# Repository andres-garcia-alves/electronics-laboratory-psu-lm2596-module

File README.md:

# Laboratory Power Supply Unit - LM2596 Module

Electronic adjustable laboratory power supply unit based on LM2596 DC-DC Step-Down module.  
Output 1.25-30V, max 2A, with current limitation feature.  

Based on videos (spanish):  
- [Control de Corriente para Fuente DC-DC LM2596](https://www.youtube.com/watch?v=ucfL-aOuTAA) from [KrissElectronics](https://www.youtube.com/@KrissElectronics) YouTube channel.
- [Fuente DC-DC LM2596, Control Externo Feedback](https://www.youtube.com/watch?v=mXjmIwHC1IA) from [Electgpl](https://www.youtube.com/@electgpl) YouTube channel.
- [Control de Corriente para DC-DC con LM2596, CC/CV con LM358](https://www.youtube.com/watch?v=a19zc0bWBYk) from [Electgpl](https://www.youtube.com/@electgpl) YouTube channel.

&nbsp;

This project use the following electronic components:
- 1 x LM2596 DC-DC Step-Down module (with current limitation).
- 1 x Voltimeter+Amperimeter DSN-VC288.
- 2 x Potenciometers B10K (lineal)
- 1 x Resistor 2.2ohm 15w.
- 2 x Borniers.
- 2 x 3 pins connectors.
- 1 x DC Jack female connector.

&nbsp;

### Screenshots

| Diagram - Schematics                                | Diagram - PCB                                       |
|-----------------------------------------------------|-----------------------------------------------------|
|              |                    |

| Diagram - PCB Render                                | Diagram - PCB Render                                |
|-----------------------------------------------------|-----------------------------------------------------|
|          |           |

| Diagram - Voltimeter/Amperimeter wiring             | Diagram - Current control wiring                    |
|-----------------------------------------------------|-----------------------------------------------------|
|  |         |

| Case - 3D Model                                     | Prototype                                           |
|-----------------------------------------------------|-----------------------------------------------------|
|               |                   |

| Project Assembly                                    | Project Assembly                                    |
|-----------------------------------------------------|-----------------------------------------------------|
|            |            |

| Project Final                                       | Project Final                                       |
|-----------------------------------------------------|-----------------------------------------------------|
|               |               |

| Project Final                                       | Project Final (YouTube video)                       |
|-----------------------------------------------------|-----------------------------------------------------|
|               |  |

See 'Rescources' sub-folder for more pictures & videos of the project.

&nbsp;

### Version History

v1.0 (2023.06.07) - Initial release.  
v1.1 (2023.06.28) - Update electronic diagrams, adding case 3D model.  
v1.2 (2023.07.08) - Adding 'Resources' folder.  
v1.3 (2025.12.26) - Adding 'Stickers' folder.  

&nbsp;

This source code is licensed under GPL v3.0  
Please send me your feedback about this project: andres.garcia.alves@gmail.com

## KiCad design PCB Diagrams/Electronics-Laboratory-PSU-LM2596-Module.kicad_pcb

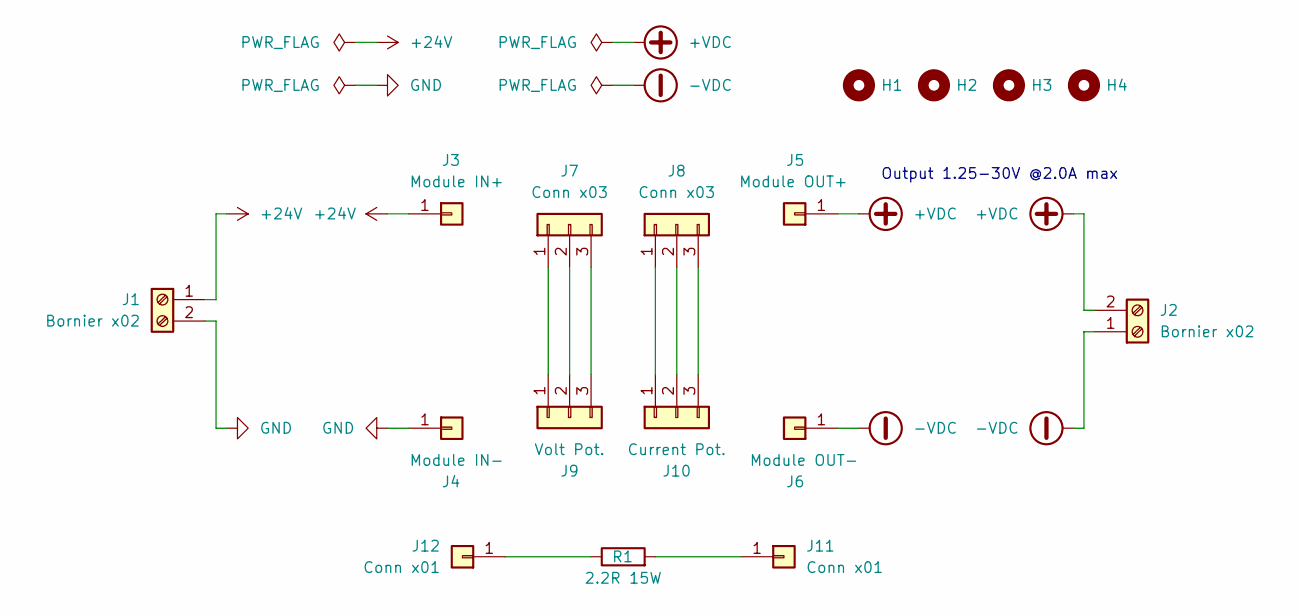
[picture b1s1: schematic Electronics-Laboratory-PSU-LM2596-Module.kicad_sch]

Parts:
H1, H2, H3, H4: MountingHole; MountingHole_2.1mm
J1, J2: Bornier x02; TerminalBlock_bornier-2_P5.08mm
J3: Module IN+; PinHeader_1x01_P2.54mm_Vertical
J4: Module IN-; PinHeader_1x01_P2.54mm_Vertical
J5: Module OUT+; PinHeader_1x01_P2.54mm_Vertical
J6: Module OUT-; PinHeader_1x01_P2.54mm_Vertical
J7, J8: Conn x03; PinHeader_1x03_P2.54mm_Vertical
J9: Volt Pot.; Molex_KK-254_AE-6410-03A_1x03_P2.54mm_Vertical
J10: Current Pot.; Molex_KK-254_AE-6410-03A_1x03_P2.54mm_Vertical
J11, J12: Conn x01; PinHeader_1x01_P2.54mm_Vertical
R1: 2.2R 15W; R_Axial_Power_L48.0mm_W12.5mm_P55.88mm

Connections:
+24V: J1.1, J3.1
+VDC: J2.2, J5.1
-VDC: J2.1, J6.1
GND: J1.2, J4.1
unnamed: J7.1, J9.1
unnamed: J7.2, J9.2
unnamed: J7.3, J9.3
unnamed: J8.1, J10.1
unnamed: J8.2, J10.2
unnamed: J8.3, J10.3
unnamed: J11.1, R1.2
unnamed: J12.1, R1.1

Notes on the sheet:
Output 1.25-30V @2.0A max

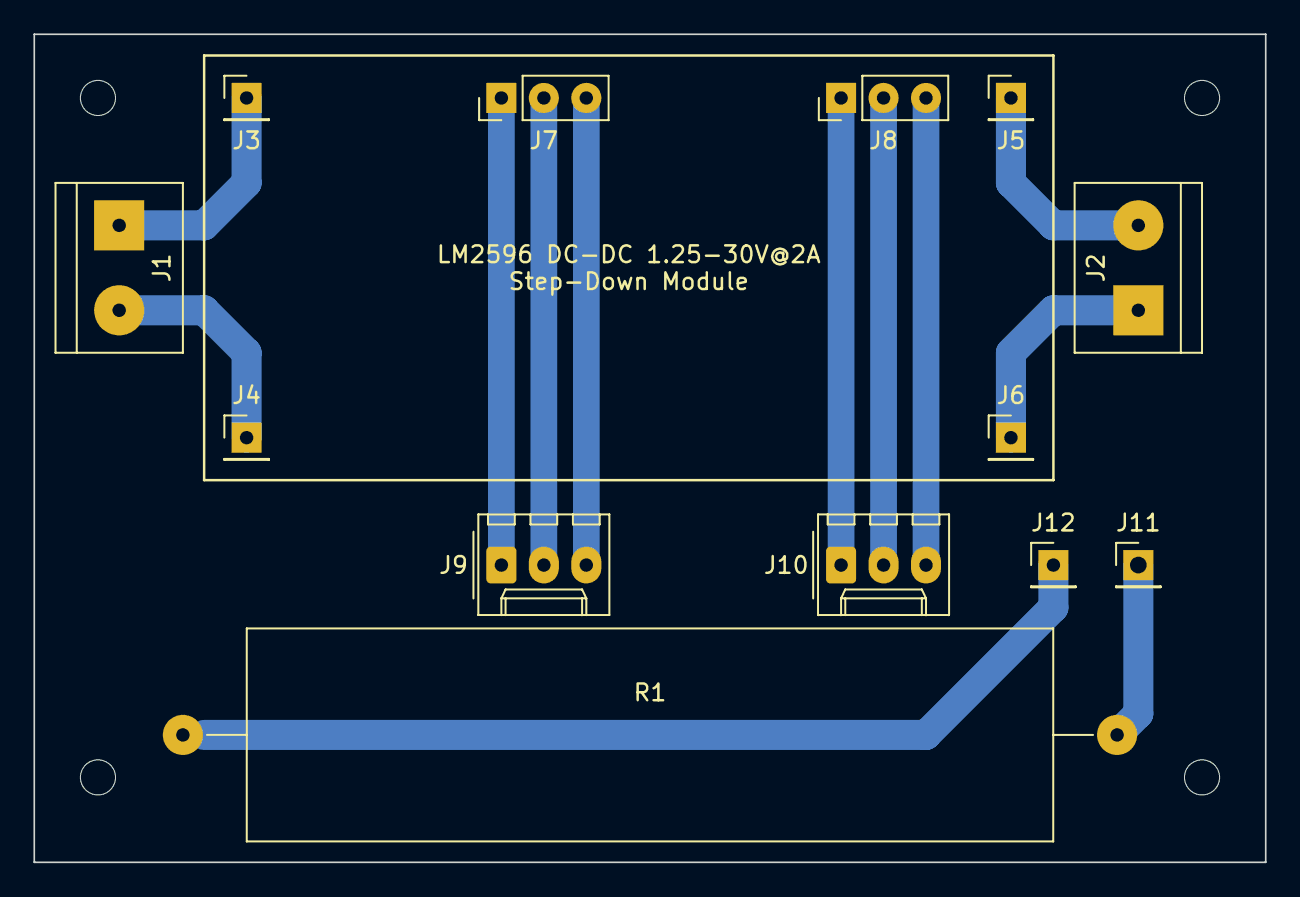
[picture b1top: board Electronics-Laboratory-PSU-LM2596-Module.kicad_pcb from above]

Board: 2 copper layers, 73.7 x 49.5 mm, 17 parts (0 on the bottom side), 12 nets.

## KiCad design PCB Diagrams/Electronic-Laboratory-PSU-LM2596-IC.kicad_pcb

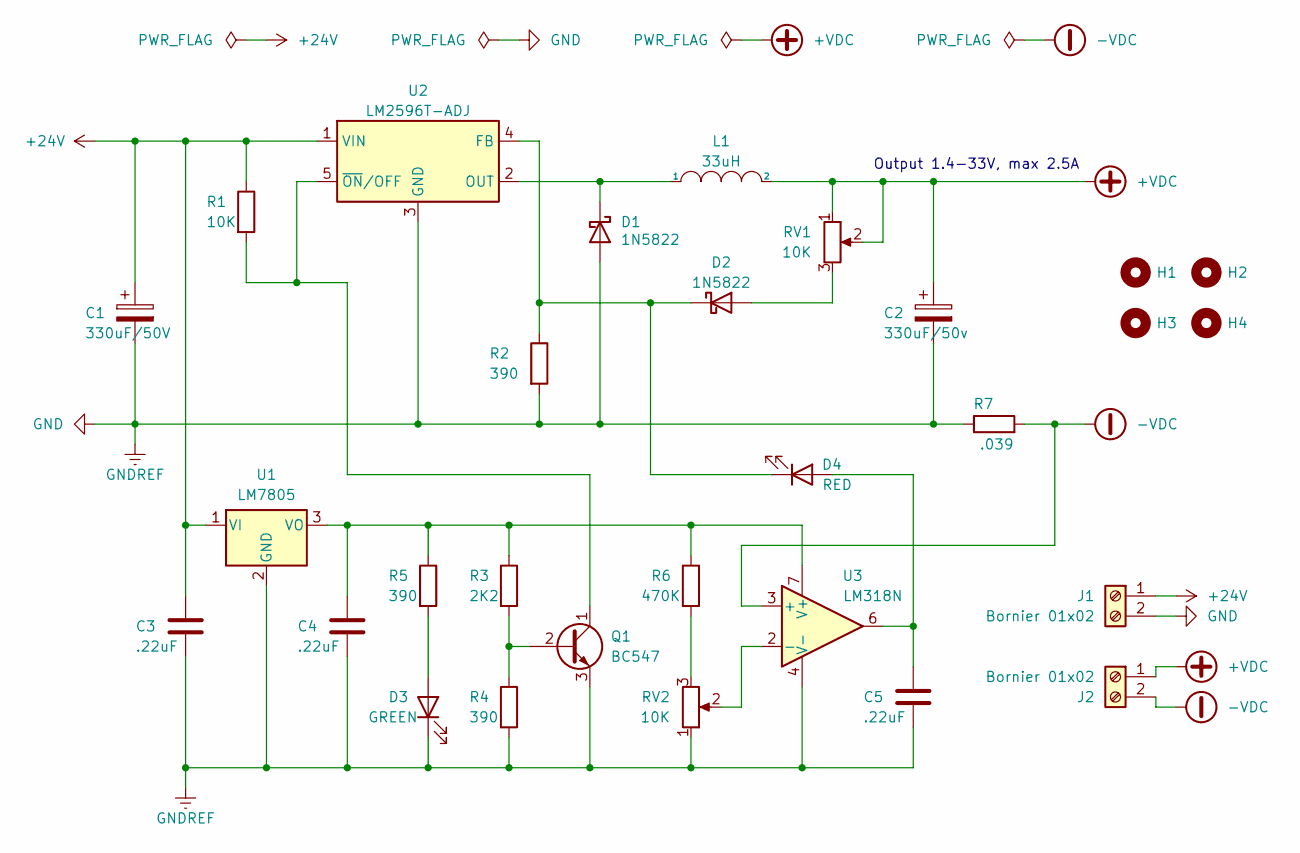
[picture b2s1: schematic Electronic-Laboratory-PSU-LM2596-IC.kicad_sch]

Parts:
C1: 330uF/50V; CP_Radial_D8.0mm_P3.80mm
C2: 330uF/50v; CP_Radial_D8.0mm_P3.80mm
C3, C4, C5: .22uF; C_Disc_D6.0mm_W2.5mm_P5.00mm
D1, D2: 1N5822; D_DO-201AD_P15.24mm_Horizontal
D3: GREEN; LED_D5.0mm
D4: RED; LED_D5.0mm
H1, H2, H3, H4: MountingHole; MountingHole_2.1mm
J1, J2: Bornier 01x02; TerminalBlock_bornier-2_P5.08mm
L1: 33uH; L_Radial_D10.0mm_P5.00mm_Fastron_07M
Q1: BC547; TO-92_Inline_Wide
R1: 10K; R_Axial_DIN0207_L6.3mm_D2.5mm_P7.62mm_Horizontal
R2, R4, R5: 390; R_Axial_DIN0207_L6.3mm_D2.5mm_P7.62mm_Horizontal
R3: 2K2; R_Axial_DIN0207_L6.3mm_D2.5mm_P7.62mm_Horizontal
R6: 470K; R_Axial_DIN0207_L6.3mm_D2.5mm_P7.62mm_Horizontal
R7: .039; R_Axial_DIN0207_L6.3mm_D2.5mm_P10.16mm_Horizontal
RV1, RV2: 10K; Potentiometer_Alps_RK163_Single_Horizontal
U1: LM7805; TO-220-3_Vertical
U2: LM2596T-ADJ; TO-220-5_P3.4x3.7mm_StaggerEven_Lead3.8mm_Vertical
U3: LM318N; DIP-8_W7.62mm

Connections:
+24V: C1.1, C3.1, J1.1, R1.1, U1.1 (VI), U2.1 (VIN)
+VDC: C2.1, J2.1, L1.2, RV1.1, RV1.2
-VDC: J2.2, R7.2, U3.3 (+)
GND: C1.2, C2.2, C3.2, C4.2, C5.2, D1.2 (A), D3.1 (K), J1.2, Q1.3 (E), R2.2, R4.2, R7.1, RV2.1, U1.2 (GND), U2.3 (GND), U3.4 (V-)
unnamed: C4.1, R3.1, R5.1, R6.1, U1.3 (VO), U3.7 (V+)
unnamed: C5.1, D4.2 (A), U3.6
unnamed: D1.1 (K), L1.1, U2.2 (OUT)
unnamed: D2.1 (K), D4.1 (K), R2.1, U2.4 (FB)
unnamed: D2.2 (A), RV1.3
unnamed: D3.2 (A), R5.2
unnamed: Q1.1 (C), R1.2, U2.5 (~ON/OFF)
unnamed: Q1.2 (B), R3.2, R4.1
unnamed: R6.2, RV2.3
unnamed: RV2.2, U3.2 (-)

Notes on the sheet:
Output 1.4-33V, max 2.5A

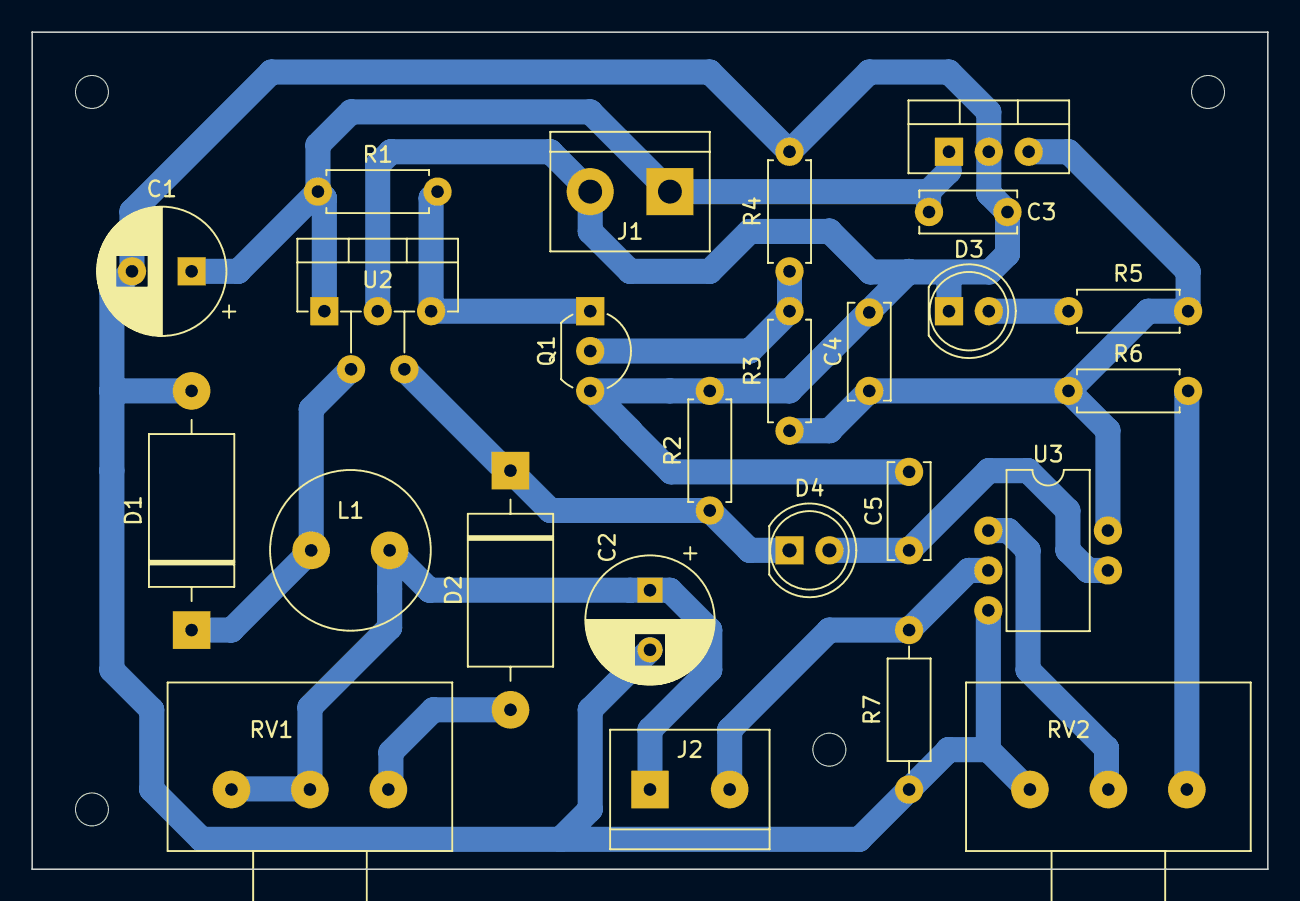
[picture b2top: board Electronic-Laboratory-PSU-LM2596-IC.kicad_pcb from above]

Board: 2 copper layers, 78.7 x 53.3 mm, 29 parts (0 on the bottom side), 14 nets.

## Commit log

2023-06-08 update PCB diagrams
2023-06-28 update electronic diagrams, adding case 3D model
2023-06-28 adding Resources
2023-06-28 update Resources
2023-06-28 update PCB diagrams, adding case 3D model
2023-07-03 adding 'Resources' files
2023-07-08 adding 'Resouces' folder
2023-07-08 adding 'Resources' folder
2025-12-26 Adding 'Stickers' folder
